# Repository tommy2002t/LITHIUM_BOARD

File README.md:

# LITHIUM_BOARD
# LITHIUM_BOARD

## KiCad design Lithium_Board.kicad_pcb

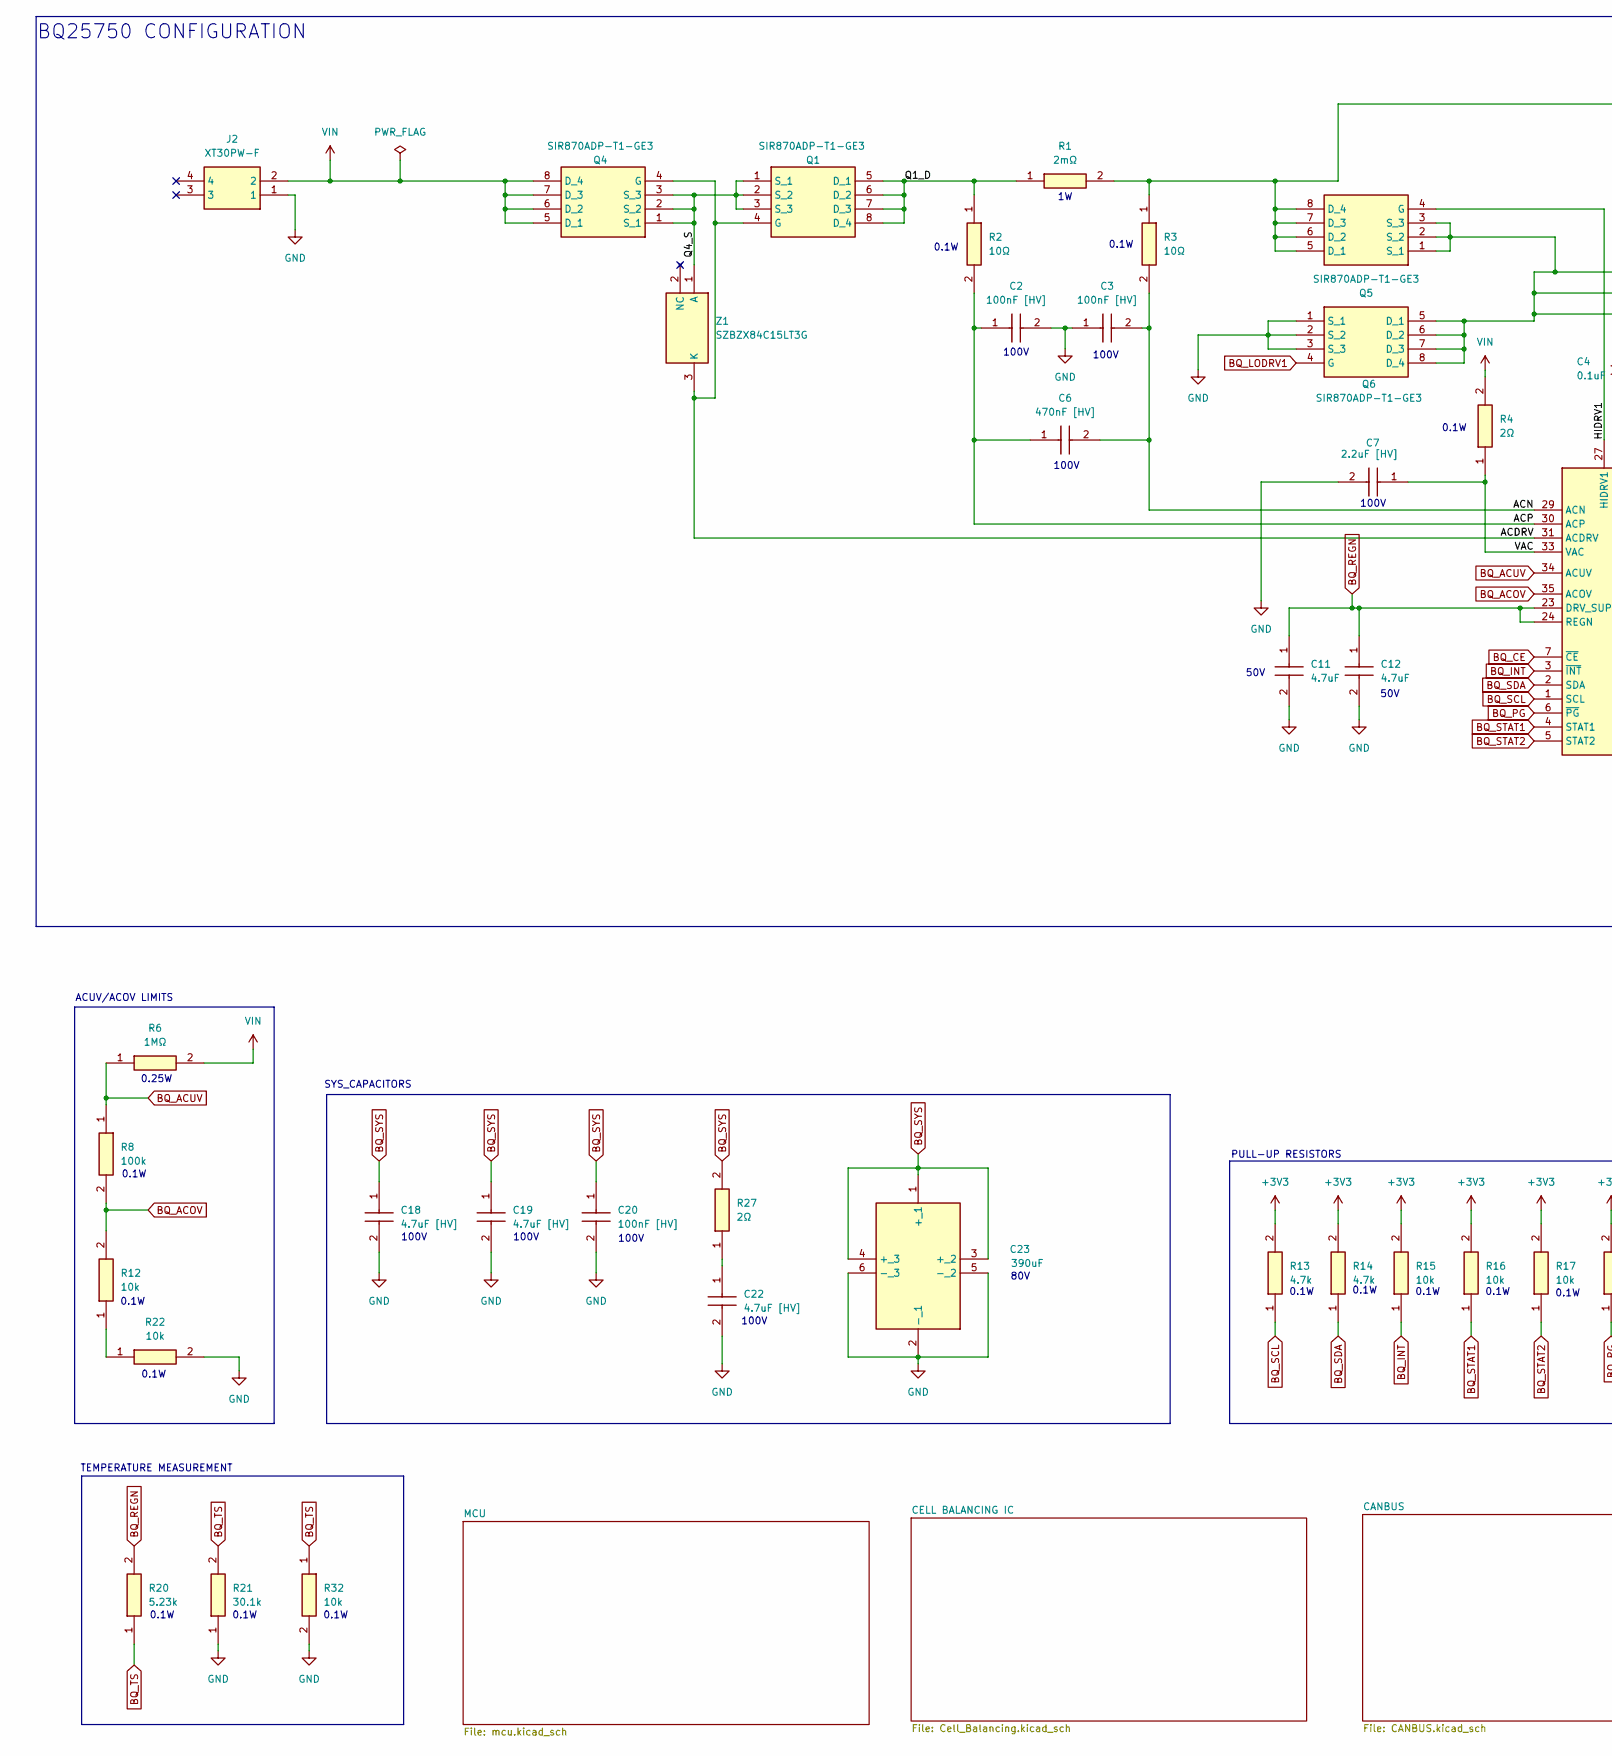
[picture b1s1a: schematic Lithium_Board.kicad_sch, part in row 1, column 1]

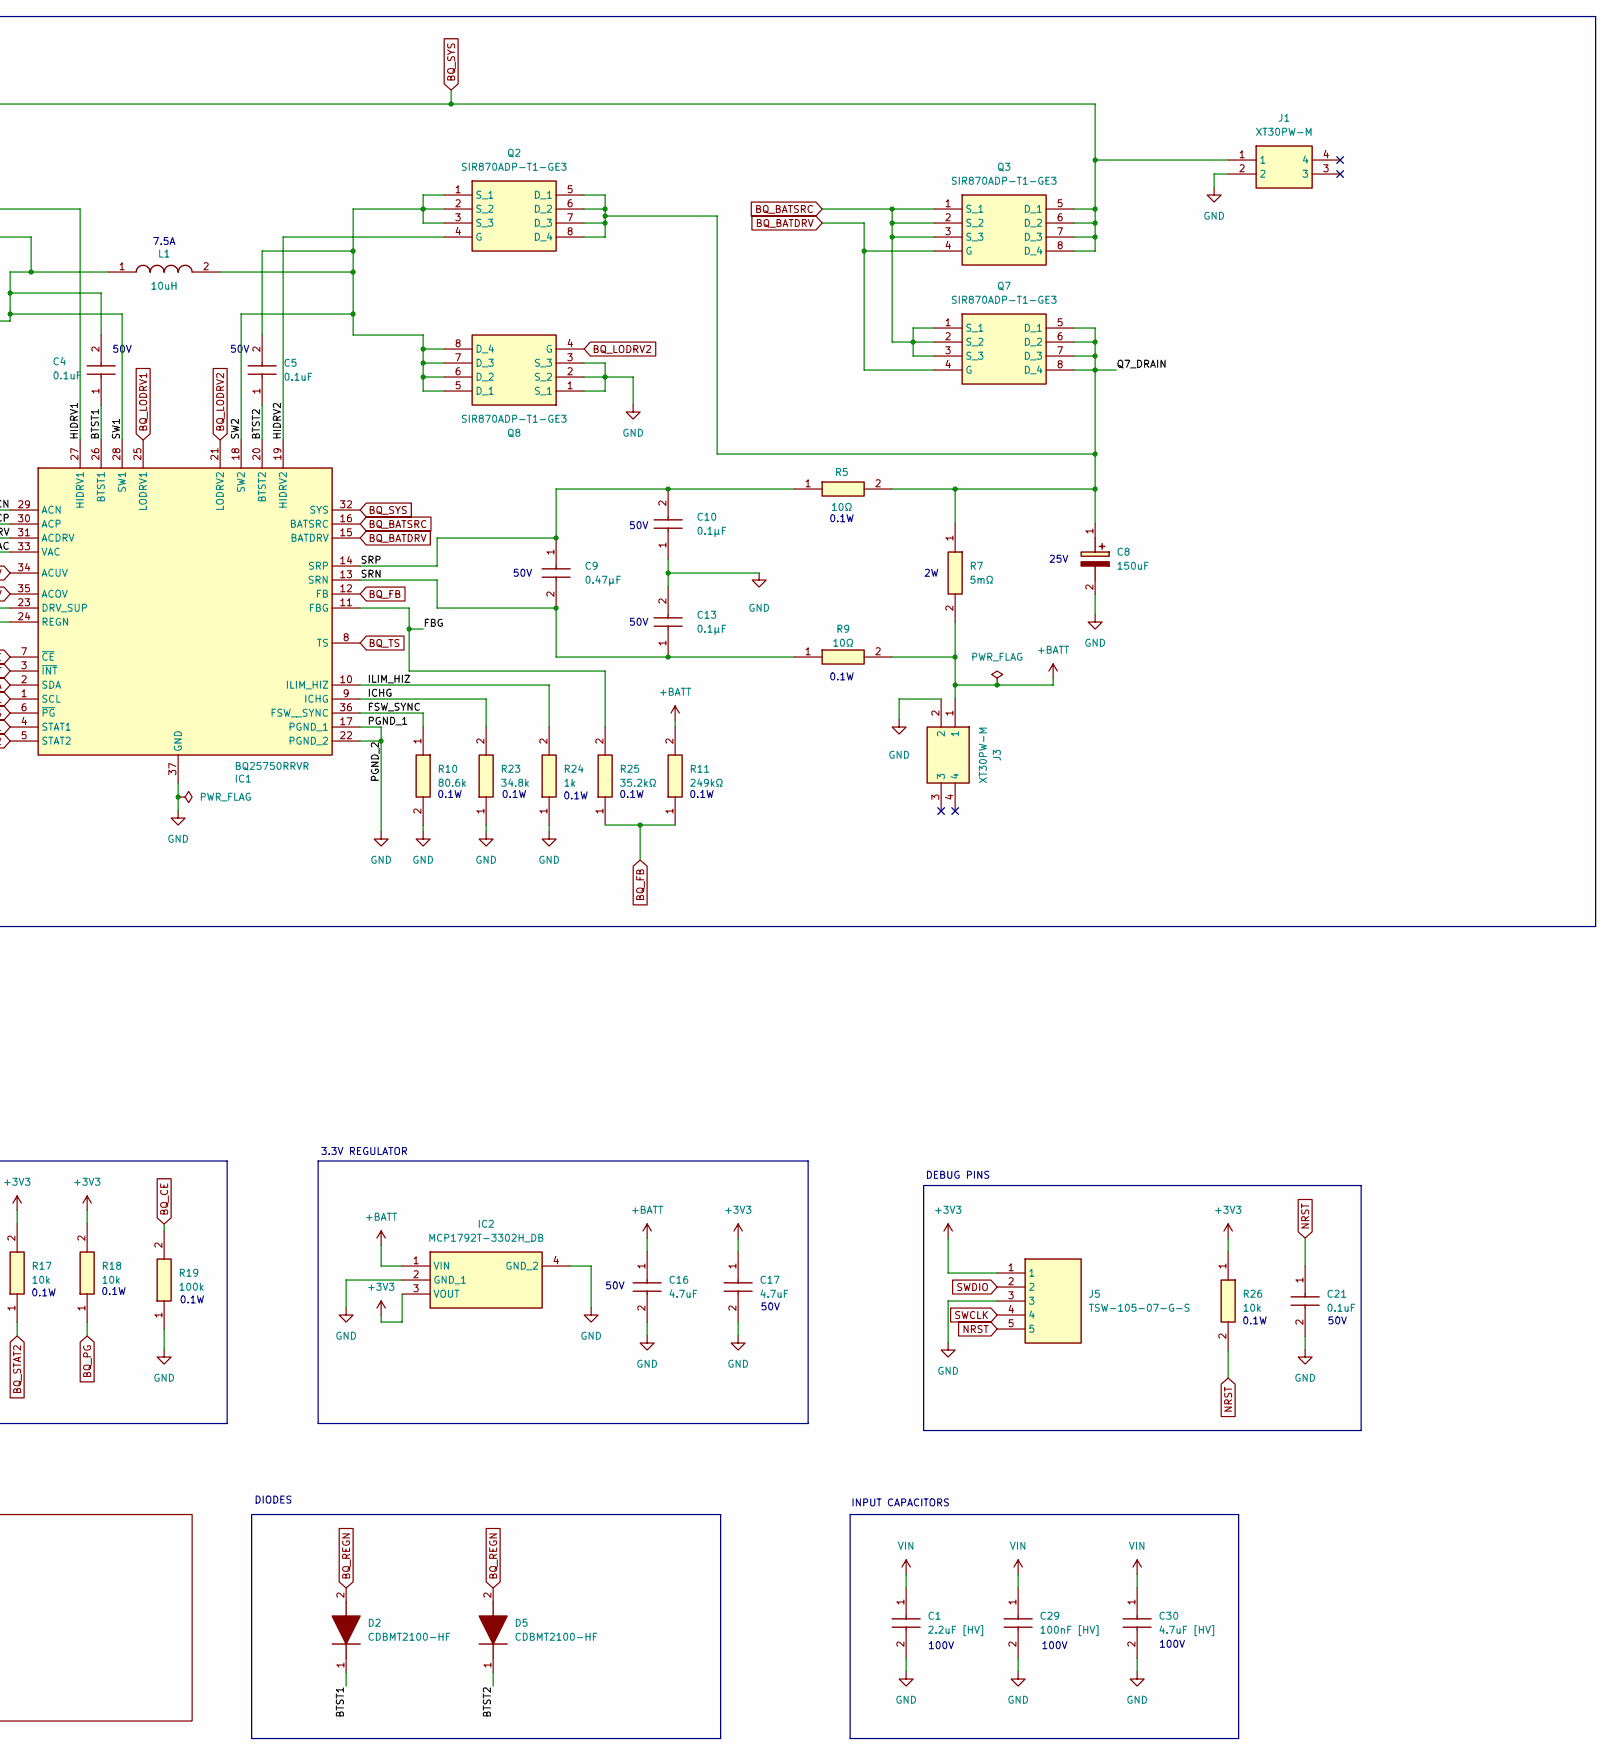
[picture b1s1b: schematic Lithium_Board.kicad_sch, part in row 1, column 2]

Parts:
C1, C7: 2.2uF [HV]; CAPC3216X180N; Mouser Part Number 187-CL31B225KCHSNNE
C2, C3, C20, C29: 100nF [HV]; CAPC1608X95N; Mouser Part Number 80-C0603C104K1RAUTO
C4, C5, C21: 0.1uF; CAPC1608X90N; Mouser Part Number 603-CC603KRX7R9BB104
C6: 470nF [HV]; CAPC3216X190N; Mouser Part Number 810-CGA5L2X7R2A474K
C8: 150uF; EEEHP1H4R7P; Manufacturer_Part_Number EEH-ZL1E151P
C9: 0.47μF; C0805; Mouser Part Number 80-C0805X474K5REAUTO
C10, C13: 0.1μF; CAPC1608X90N; Mouser Part Number 603-CC603KRX7R9BB104
C11, C12, C16, C17: 4.7uF; CAPC3225X280N; Mouser Part Number 963-UMJ325AB7475KMHP
C18, C19, C22, C30: 4.7uF [HV]; CAPC3225X94N; Mouser Part Number 581-KAM32LR72A475KU
C23: 390uF; EEEFK0J682AV; Mouser Part Number 667-EEE-TP1K391V
D2, D5: CDBMT2100-HF; SODFL3516X100N; Mouser Part Number 750-CDBMT2100-HF
IC1: BQ25750RRVR; QFN50P500X600X100-37N-D; Mouser Part Number 595-BQ25750RRVR
IC2: MCP1792T-3302H_DB; SOT230P700X180-4N; Mouser Part Number 579-MCP1792T-3302HDB
J1, J3: XT30PW-M; XT30PWM; Manufacturer_Part_Number XT30PW-M
J2: XT30PW-F; XT30PWF; Manufacturer_Part_Number XT30PW-F
J5: TSW-105-07-G-S; TSW-105-XX-YY-S; Mouser Part Number 200-TSW10507GS
L1: 10uH; INDPM110100X400N; Mouser Part Number 652-SRP1038A-100M
Q1, Q2, Q3, Q4, Q5, Q6, Q7, Q8: SIR870ADP-T1-GE3; POWERPAK-SO-8; Mouser Part Number 78-SIR870ADP-T1-GE3
R1: 2mΩ; RESC3216X59N; Mouser Part Number 755-PMR18EZPFV2L00
R2, R3, R5, R9: 10Ω; RESC1608X55N; Mouser Part Number 603-RC0603FR-0710RL
R4, R27: 2Ω; RESC1608X55N; Mouser Part Number 603-RC0603FR-072RL
R6: 1MΩ; RESC3116X65N; Mouser Part Number 603-VT1206BRD071ML
R7: 5mΩ; RESC6432X67N; Mouser Part Number 755-PMR100HZPFU5L00
R8, R19: 100k; RESC1608X55N; Mouser Part Number 603-RC0603FR-07100KL
R10: 80.6k; RESC1608X55N; Mouser Part Number 603-RC0603FR-0780K6L
R11: 249kΩ; RESC1608X55N; Mouser Part Number 603-RT0603BRD07249KL
R12, R15, R16, R17, R18, R22, R26, R32: 10k; RESC1608X55N; Mouser Part Number 603-RC0603FR-0710KL
R13, R14: 4.7k; RESC1608X55N; Mouser Part Number 603-RC0603FR-074K7L
R20: 5.23k; RESC1608X55N; Mouser Part Number 603-RC0603FR-075K23L
R21: 30.1k; RESC1608X55N; Mouser Part Number 603-RC0603FR-0730K1L
R23: 34.8k; RESC1608X55N; Mouser Part Number 603-RC0603FR-0734K8L
R24: 1k; RESC1608X55N; Mouser Part Number 603-RC0603FR-071KL
R25: 35.2kΩ; RESC1608X55N; Manufacturer_Part_Number RT0603BRD0735K2L
Z1: SZBZX84C15LT3G; SOT96P237X111-3N; Mouser Part Number 863-SZBZX84C15LT3G

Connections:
+3V3: C17.1, IC2.3 (VOUT), J5.1, R13.2, R14.2, R15.2, R16.2, R17.2, R18.2, R26.1; also elsewhere on the board
+BATT: C16.1, IC2.1 (VIN), J3.1, R7.2, R9.2, R11.2
/ACDRV: IC1.31 (ACDRV), Q1.4 (G), Q4.4 (G), Z1.3 (K)
/ACN: C3.2, C6.2, IC1.29 (ACN), R3.2
/ACP: C2.1, C6.1, IC1.30 (ACP), R2.2
/BTST1: C4.1, D2.1 (K), IC1.26 (BTST1)
/BTST2: C5.1, D5.1 (K), IC1.20 (BTST2)
/FBG: IC1.11 (FBG), R25.2
/FSW_SYNC: IC1.36 (FSW__SYNC), R10.1
/HIDRV1: IC1.27 (HIDRV1), Q5.4 (G)
/HIDRV2: IC1.19 (HIDRV2), Q2.4 (G)
/ICHG: IC1.9 (ICHG), R23.2
/ILIM_HIZ: IC1.10 (ILIM_HIZ), R24.2
/Q1_D: Q1.5 (D_1), Q1.6 (D_2), Q1.7 (D_3), Q1.8 (D_4), R1.1, R2.1
/Q4_S: Q1.1 (S_1), Q1.2 (S_2), Q1.3 (S_3), Q4.1 (S_1), Q4.2 (S_2), Q4.3 (S_3), Z1.1 (A)
/Q7_DRAIN: C8.1 (+), Q2.5 (D_1), Q2.6 (D_2), Q2.7 (D_3), Q2.8 (D_4), Q7.5 (D_1), Q7.6 (D_2), Q7.7 (D_3), Q7.8 (D_4), R5.2, R7.1
/SRN: C9.2, C13.1, IC1.13 (SRN), R9.1
/SRP: C9.1, C10.2, IC1.14 (SRP), R5.1
/SW1: C4.2, IC1.28 (SW1), L1.1, Q5.1 (S_1), Q5.2 (S_2), Q5.3 (S_3), Q6.5 (D_1), Q6.6 (D_2), Q6.7 (D_3), Q6.8 (D_4)
/SW2: C5.2, IC1.18 (SW2), L1.2, Q2.1 (S_1), Q2.2 (S_2), Q2.3 (S_3), Q8.5 (D_1), Q8.6 (D_2), Q8.7 (D_3), Q8.8 (D_4)
/VAC: C7.1, IC1.33 (VAC), R4.1
BQ_ACOV: IC1.35 (ACOV), R8.2, R12.2
BQ_ACUV: IC1.34 (ACUV), R6.1, R8.1
BQ_BATDRV: IC1.15 (BATDRV), Q3.4 (G), Q7.4 (G)
BQ_BATSRC: IC1.16 (BATSRC), Q3.1 (S_1), Q3.2 (S_2), Q3.3 (S_3), Q7.1 (S_1), Q7.2 (S_2), Q7.3 (S_3)
BQ_CE: IC1.7 (~CE), R19.2; also elsewhere on the board
BQ_FB: IC1.12 (FB), R11.1, R25.1
BQ_INT: IC1.3 (~INT), R15.1; also elsewhere on the board
BQ_LODRV1: IC1.25 (LODRV1), Q6.4 (G)
BQ_LODRV2: IC1.21 (LODRV2), Q8.4 (G)
BQ_PG: IC1.6 (~PG), R18.1; also elsewhere on the board
BQ_REGN: C11.1, C12.1, D2.2 (A), D5.2 (A), IC1.23 (DRV_SUP), IC1.24 (REGN), R20.2
BQ_SCL: IC1.1 (SCL), R13.1; also elsewhere on the board
BQ_SDA: IC1.2 (SDA), R14.1; also elsewhere on the board
BQ_STAT1: IC1.4 (STAT1), R16.1; also elsewhere on the board
BQ_STAT2: IC1.5 (STAT2), R17.1; also elsewhere on the board
BQ_SYS: C18.1, C19.1, C20.1, C23.1 (+_1), C23.3 (+_2), C23.4 (+_3), IC1.32 (SYS), J1.1, Q3.5 (D_1), Q3.6 (D_2), Q3.7 (D_3), Q3.8 (D_4), Q5.5 (D_1), Q5.6 (D_2), Q5.7 (D_3), Q5.8 (D_4), R1.2, R3.1, R27.2
BQ_TS: IC1.8 (TS), R20.1, R21.2, R32.1; also elsewhere on the board
GND: C1.2, C2.2, C3.1, C7.2, C8.2 (-), C10.1, C11.2, C12.2, C13.2, C16.2, C17.2, C18.2, C19.2, C20.2, C21.2, C22.2, C23.2 (-_1), C23.5 (-_2), C23.6 (-_3), C29.2, C30.2, IC1.17 (PGND_1), IC1.22 (PGND_2), IC1.37 (GND), IC2.2 (GND_1), IC2.4 (GND_2), J1.2, J2.1, J3.2, J5.3, Q6.1 (S_1), Q6.2 (S_2), Q6.3 (S_3), Q8.1 (S_1), Q8.2 (S_2), Q8.3 (S_3), R10.2, R19.1, R21.1, R22.2, R23.1, R24.1, R32.2; also elsewhere on the board
NRST: C21.1, J5.5, R26.2; also elsewhere on the board
unnamed: C22.1, R27.1
unnamed: R12.1, R22.1
SWCLK: J5.4; also elsewhere on the board
SWDIO: J5.2; also elsewhere on the board
VIN: C1.1, C29.1, C30.1, J2.2, Q4.5 (D_1), Q4.6 (D_2), Q4.7 (D_3), Q4.8 (D_4), R4.2, R6.2

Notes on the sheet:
0.1W
TEMPERATURE MEASUREMENT
50V
ACUV/ACOV LIMITS
INPUT CAPACITORS
100V
PULL-UP RESISTORS
DEBUG PINS
7.5A
3.3V REGULATOR
DIODES
25V
80V
SYS_CAPACITORS
0.25W
BQ25750 CONFIGURATION

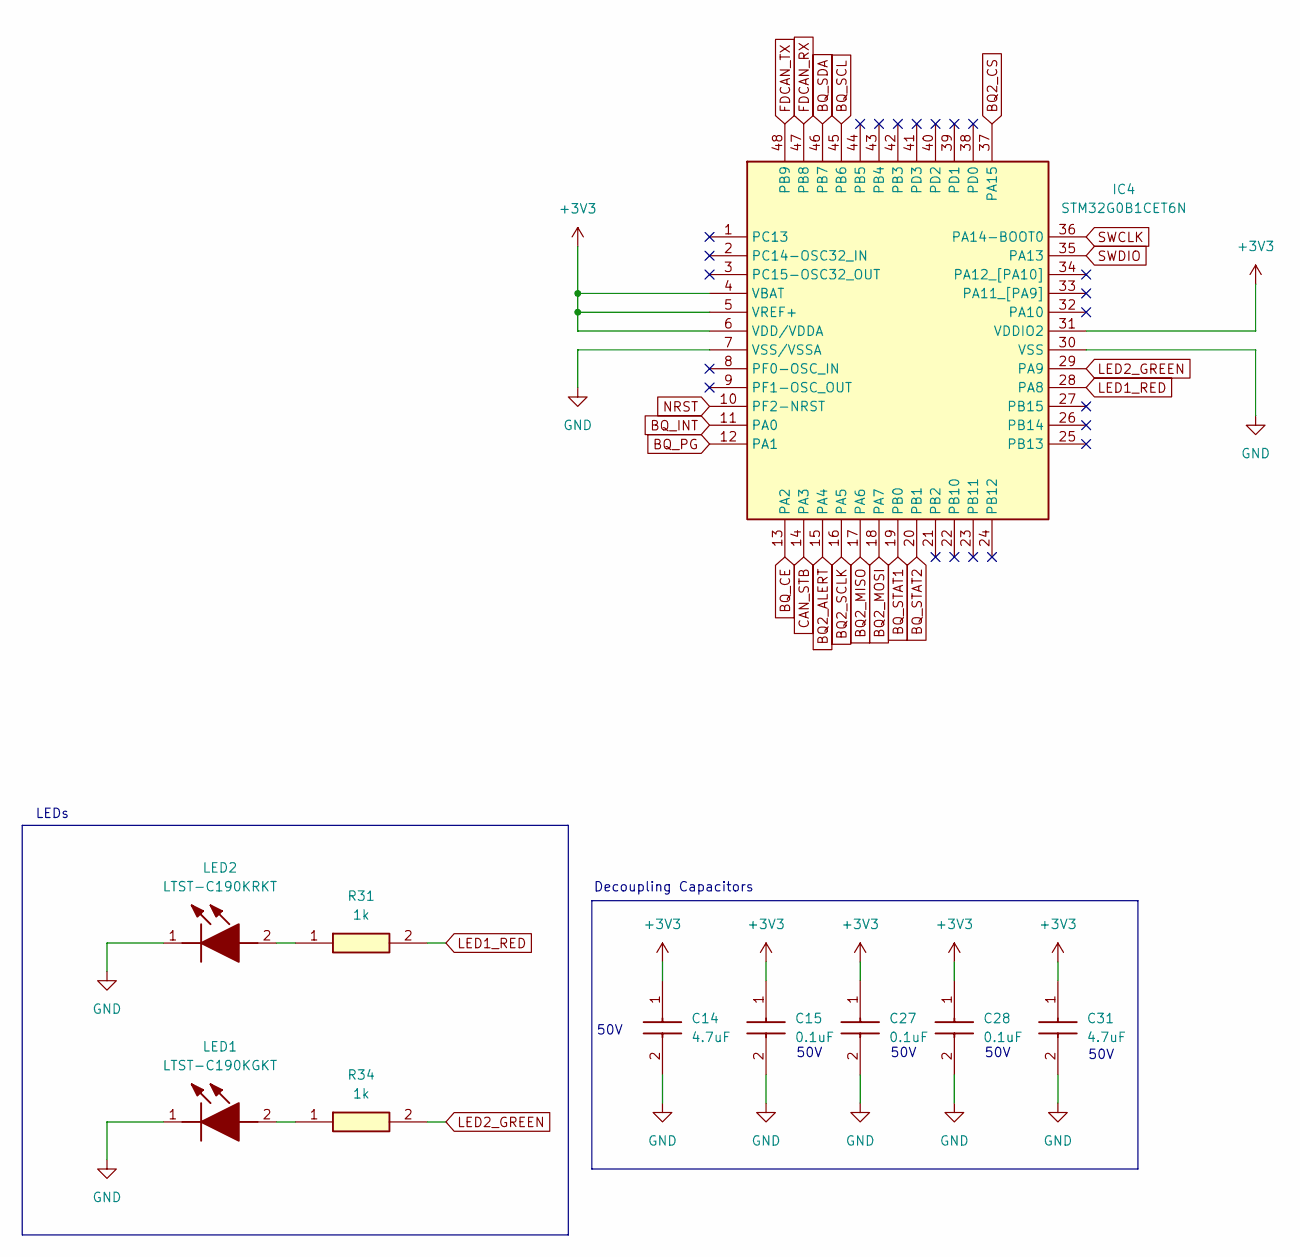
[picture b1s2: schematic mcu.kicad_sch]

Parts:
C14, C31: 4.7uF; CAPC3225X280N; Mouser Part Number 963-UMJ325AB7475KMHP
C15, C27, C28: 0.1uF; CAPC1608X90N; Mouser Part Number 603-CC603KRX7R9BB104
IC4: STM32G0B1CET6N; QFP50P900X900X160-48N; Mouser Part Number 511-STM32G0B1CET6N
LED1: LTST-C190KGKT; LEDC1608X80N; Mouser Part Number 859-LTST-C190KGKT
LED2: LTST-C190KRKT; LEDC1608X80N; Mouser Part Number 859-LTST-C190KRKT
R31, R34: 1k; RESC1608X55N; Mouser Part Number 603-RC0603FR-071KL

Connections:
+3V3: C14.1, C15.1, C27.1, C28.1, C31.1, IC4.4 (VBAT), IC4.5 (VREF+), IC4.6 (VDD/VDDA), IC4.31 (VDDIO2); also elsewhere on the board
BQ2_ALERT: IC4.15 (PA4); also elsewhere on the board
BQ2_CS: IC4.37 (PA15); also elsewhere on the board
BQ2_MISO: IC4.17 (PA6); also elsewhere on the board
BQ2_MOSI: IC4.18 (PA7); also elsewhere on the board
BQ2_SCLK: IC4.16 (PA5); also elsewhere on the board
BQ_CE: IC4.13 (PA2); also elsewhere on the board
BQ_INT: IC4.11 (PA0); also elsewhere on the board
BQ_PG: IC4.12 (PA1); also elsewhere on the board
BQ_SCL: IC4.45 (PB6); also elsewhere on the board
BQ_SDA: IC4.46 (PB7); also elsewhere on the board
BQ_STAT1: IC4.19 (PB0); also elsewhere on the board
BQ_STAT2: IC4.20 (PB1); also elsewhere on the board
CAN_STB: IC4.14 (PA3); also elsewhere on the board
FDCAN_RX: IC4.47 (PB8); also elsewhere on the board
FDCAN_TX: IC4.48 (PB9); also elsewhere on the board
GND: C14.2, C15.2, C27.2, C28.2, C31.2, IC4.7 (VSS/VSSA), IC4.30 (VSS), LED1.1 (K), LED2.1 (K); also elsewhere on the board
LED1_RED: IC4.28 (PA8), R31.2
LED2_GREEN: IC4.29 (PA9), R34.2
NRST: IC4.10 (PF2-NRST); also elsewhere on the board
unnamed: LED1.2 (A), R34.1
unnamed: LED2.2 (A), R31.1
SWCLK: IC4.36 (PA14-BOOT0); also elsewhere on the board
SWDIO: IC4.35 (PA13); also elsewhere on the board

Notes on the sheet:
Decoupling Capacitors
50V
LEDs

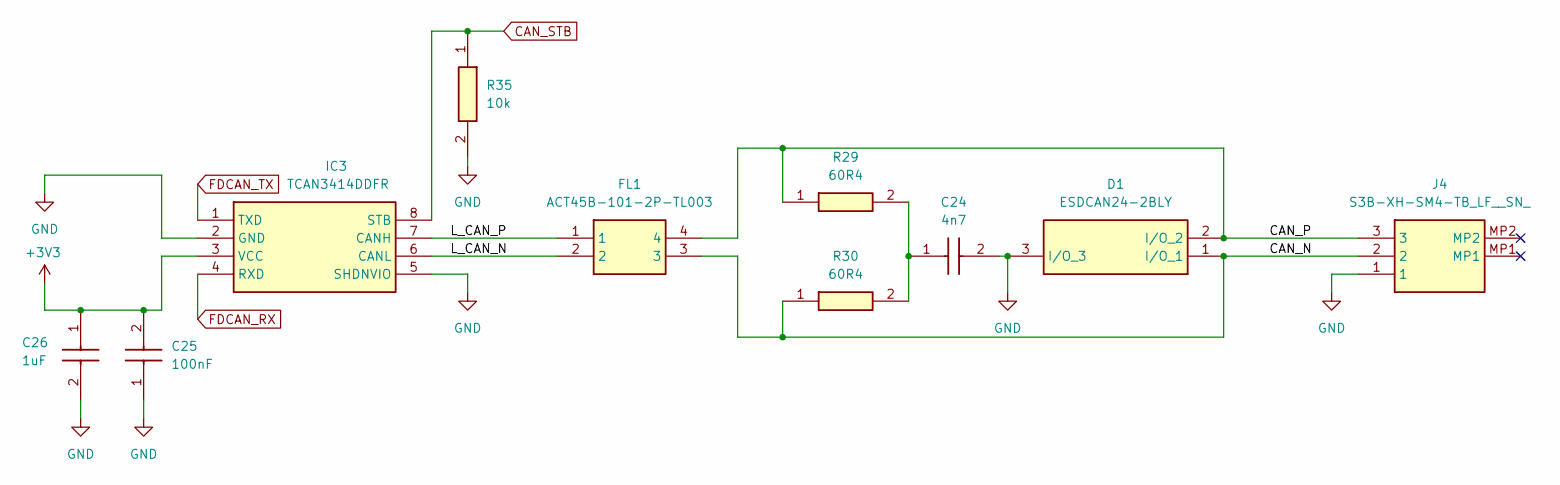
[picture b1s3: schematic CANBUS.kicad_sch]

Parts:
C24: 4n7; CAPC1608X90N; Mouser Part Number 81-GRM188R72A472KA1D
C25: 100nF; GRM15x; Mouser Part Number 81-GRM155R71H104KE4J
C26: 1uF; CAPC2012X145N; Mouser Part Number 810-C2012X7R1H105K
D1: ESDCAN24-2BLY; SOT95P255X125-3N; Mouser Part Number 511-ESDCAN24-2BLY
FL1: ACT45B-101-2P-TL003; ACT45B1012PTL003; Mouser Part Number 810-ACT45B1012PTL003
IC3: TCAN3414DDFR; INA190A2NDDFREP; Mouser Part Number 595-TCAN3414DDFR
J4: S3B-XH-SM4-TB_LF__SN_; S3BXHSM4TBLFSN; Mouser Part Number N/A
R29, R30: 60R4; ERJ2RKD1004X; Mouser Part Number 667-ERJ-2RKF60R4X
R35: 10k; RESC1608X55N; Mouser Part Number 603-RC0603FR-0710KL

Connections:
+3V3: C25.2, C26.1, IC3.3 (VCC); also elsewhere on the board
/CANBUS/CAN_N: D1.1 (I/O), FL1.3, J4.2, R30.1
/CANBUS/CAN_P: D1.2 (I/O), FL1.4, J4.3, R29.1
/CANBUS/L_CAN_N: FL1.2, IC3.6 (CANL)
/CANBUS/L_CAN_P: FL1.1, IC3.7 (CANH)
CAN_STB: IC3.8 (STB), R35.1; also elsewhere on the board
FDCAN_RX: IC3.4 (RXD); also elsewhere on the board
FDCAN_TX: IC3.1 (TXD); also elsewhere on the board
GND: C24.2, C25.1, C26.2, D1.3 (I/O), IC3.2 (GND), IC3.5 (SHDNVIO), J4.1, R35.2; also elsewhere on the board
unnamed: C24.1, R29.2, R30.2

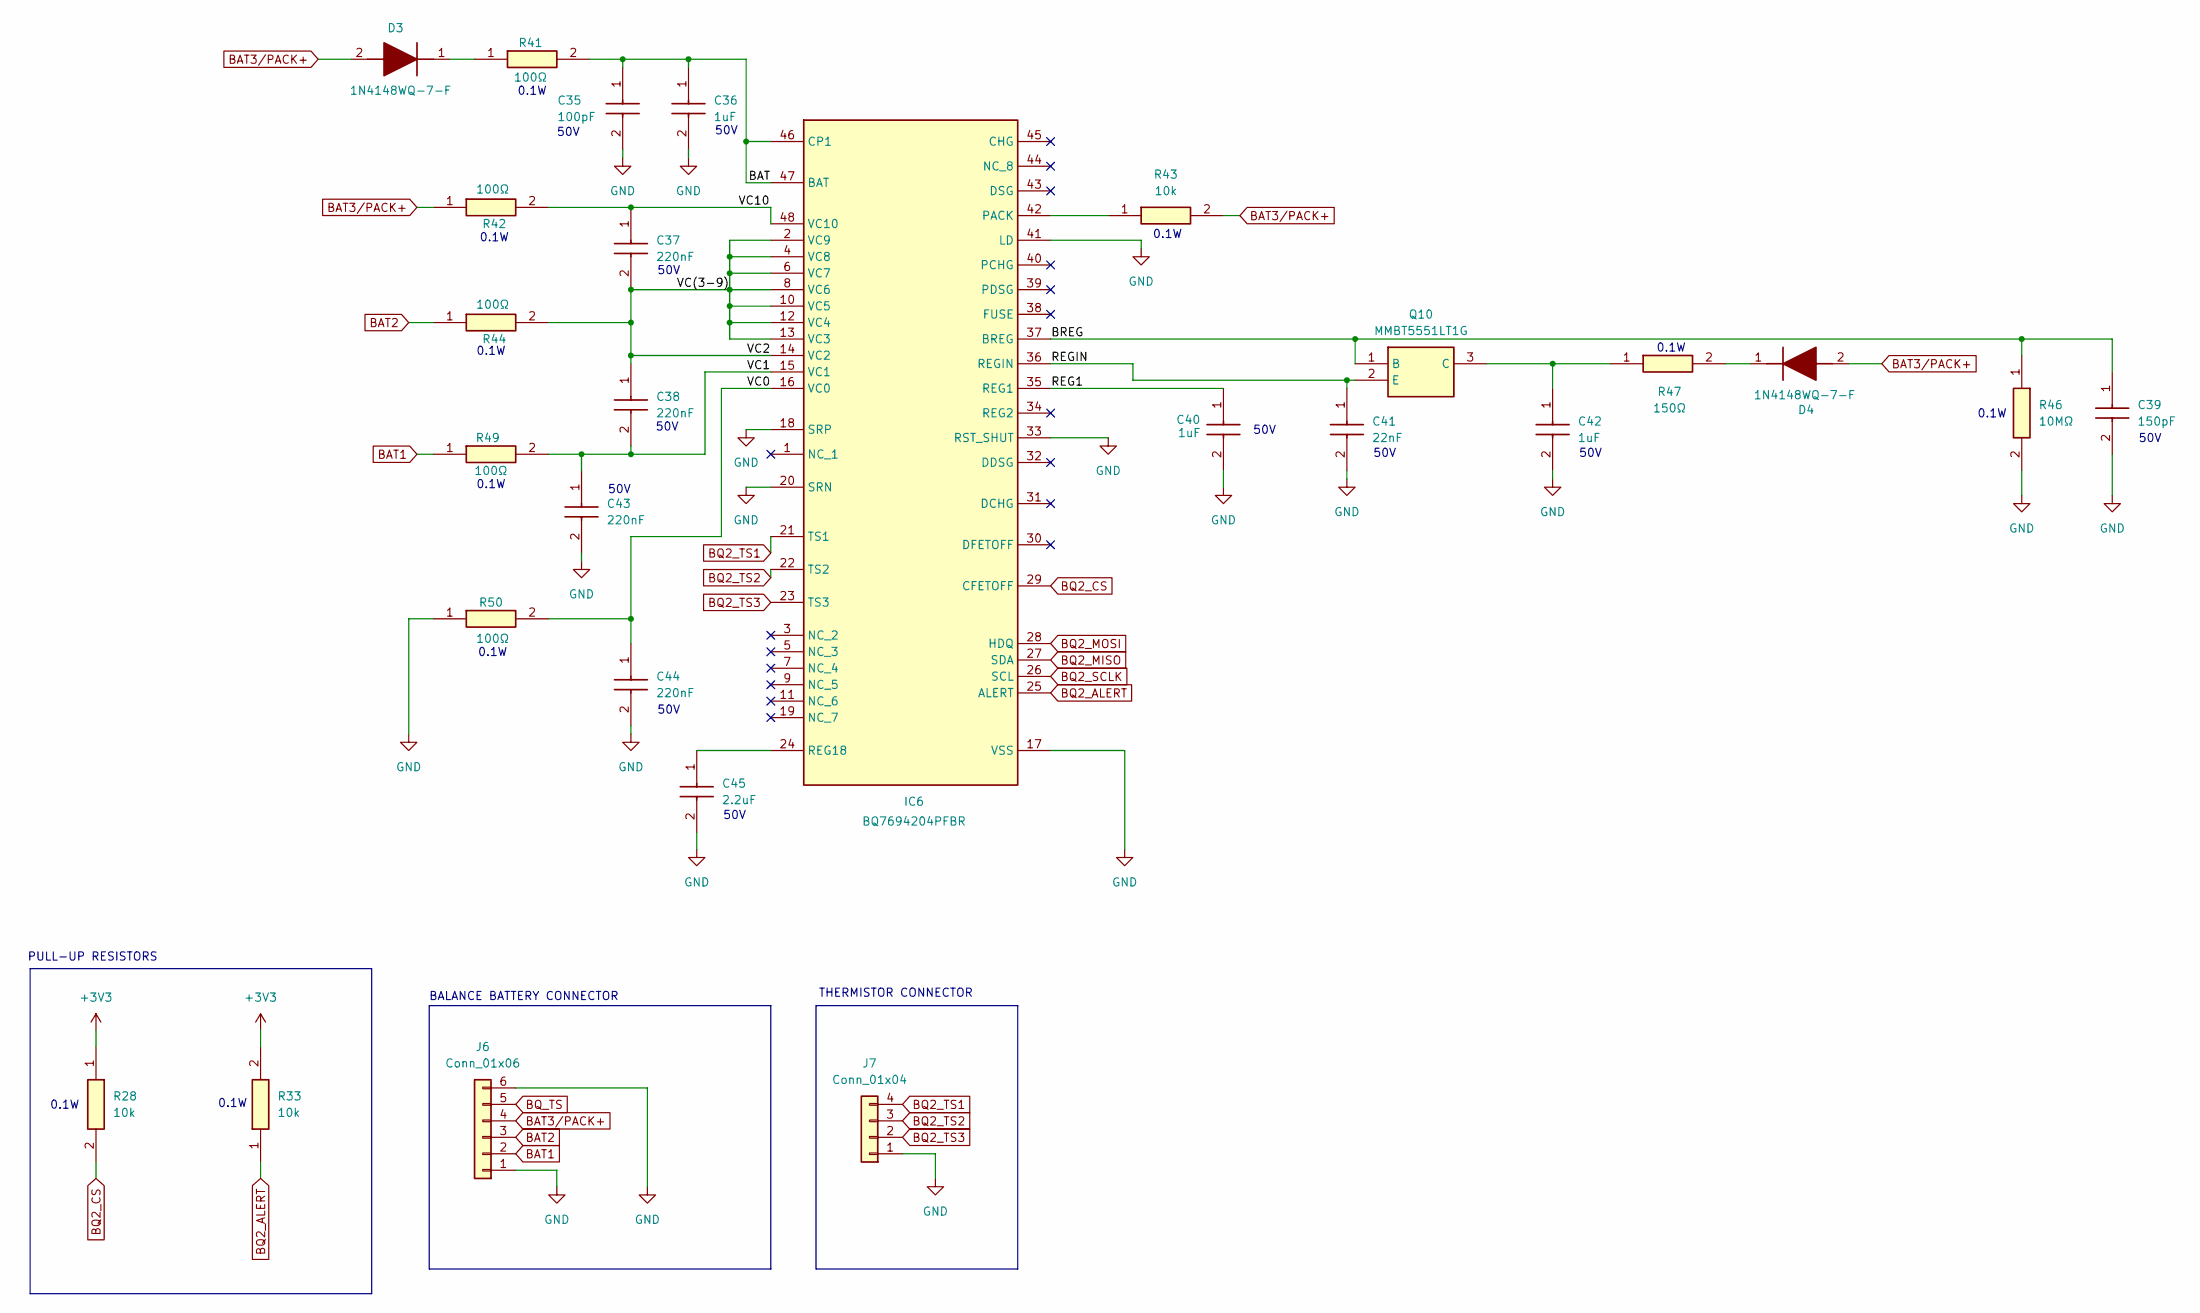
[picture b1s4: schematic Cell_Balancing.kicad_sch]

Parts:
C35: 100pF; CAPC1608X87N; Mouser Part Number 80-C0603C101J5G
C36, C40, C42: 1uF; CAPC2012X145N; Mouser Part Number 810-C2012X7R1H105K
C37, C38, C43, C44: 220nF; C0805; Mouser Part Number 80-C0805C224K5R
C39: 150pF; CAPC1608X87N; Mouser Part Number 80-C0603C151J5G
C41: 22nF; C0603; Mouser Part Number 80-C0603C223K5R
C45: 2.2uF; C1206; Mouser Part Number 80-C1206C225K5R
D3, D4: 1N4148WQ-7-F; SOD3716X145N; Mouser Part Number 621-1N4148WQ-7-F
IC6: BQ7694204PFBR; QFP50P900X900X120-48N; Mouser Part Number 595-BQ7694204PFBR
J6: Conn_01x06; JST_XH_B6B-XH-A_1x06_P2.50mm_Vertical
J7: Conn_01x04; JST_XH_B4B-XH-A_1x04_P2.50mm_Vertical
Q10: MMBT5551LT1G; SOT96P237X111-3N; Mouser Part Number 863-MMBT5551LT1G
R28, R33, R43: 10k; RESC1608X55N; Mouser Part Number 603-RC0603FR-0710KL
R41, R42, R44, R49, R50: 100Ω; RESC1608X55N; Mouser Part Number 603-RC0603FR-07100RL
R46: 10MΩ; RESC1608X55N; Mouser Part Number 603-RC0603FR-0710ML
R47: 150Ω; RESC1608X55N; Mouser Part Number 603-RC0603FR-07150RL

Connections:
+3V3: R28.1, R33.2; also elsewhere on the board
/CELL BALANCING IC/BAT: C35.1, C36.1, IC6.46 (CP1), IC6.47 (BAT), R41.2
/CELL BALANCING IC/BREG: C39.1, IC6.37 (BREG), Q10.1 (B), R46.1
/CELL BALANCING IC/REG1: C40.1, IC6.35 (REG1)
/CELL BALANCING IC/REGIN: C41.1, IC6.36 (REGIN), Q10.2 (E)
/CELL BALANCING IC/VC0: C44.1, IC6.16 (VC0), R50.2
/CELL BALANCING IC/VC1: C38.2, C43.1, IC6.15 (VC1), R49.2
/CELL BALANCING IC/VC10: C37.1, IC6.48 (VC10), R42.2
/CELL BALANCING IC/VC(3-9): C37.2, C38.1, IC6.2 (VC9), IC6.4 (VC8), IC6.6 (VC7), IC6.8 (VC6), IC6.10 (VC5), IC6.12 (VC4), IC6.13 (VC3), IC6.14 (VC2), R44.2
BAT1: J6.2, R49.1
BAT2: J6.3, R44.1
BAT3/PACK+: D3.2 (A), D4.2 (A), J6.4, R42.1, R43.2
BQ2_ALERT: IC6.25 (ALERT), R33.1; also elsewhere on the board
BQ2_CS: IC6.29 (CFETOFF), R28.2; also elsewhere on the board
BQ2_MISO: IC6.27 (SDA); also elsewhere on the board
BQ2_MOSI: IC6.28 (HDQ); also elsewhere on the board
BQ2_SCLK: IC6.26 (SCL); also elsewhere on the board
BQ2_TS1: IC6.21 (TS1), J7.4
BQ2_TS2: IC6.22 (TS2), J7.3
BQ2_TS3: IC6.23 (TS3), J7.2
BQ_TS: J6.5; also elsewhere on the board
GND: C35.2, C36.2, C39.2, C40.2, C41.2, C42.2, C43.2, C44.2, C45.2, IC6.17 (VSS), IC6.18 (SRP), IC6.20 (SRN), IC6.33 (RST_SHUT), IC6.41 (LD), J6.1, J6.6, J7.1, R46.2, R50.1; also elsewhere on the board
unnamed: D3.1 (K), R41.1
unnamed: D4.1 (K), R47.2
unnamed: IC6.42 (PACK), R43.1
unnamed: C45.1, IC6.24 (REG18)
unnamed: C42.1, Q10.3 (C), R47.1

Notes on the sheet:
50V
0.1W
PULL-UP RESISTORS
BALANCE BATTERY CONNECTOR
THERMISTOR CONNECTOR

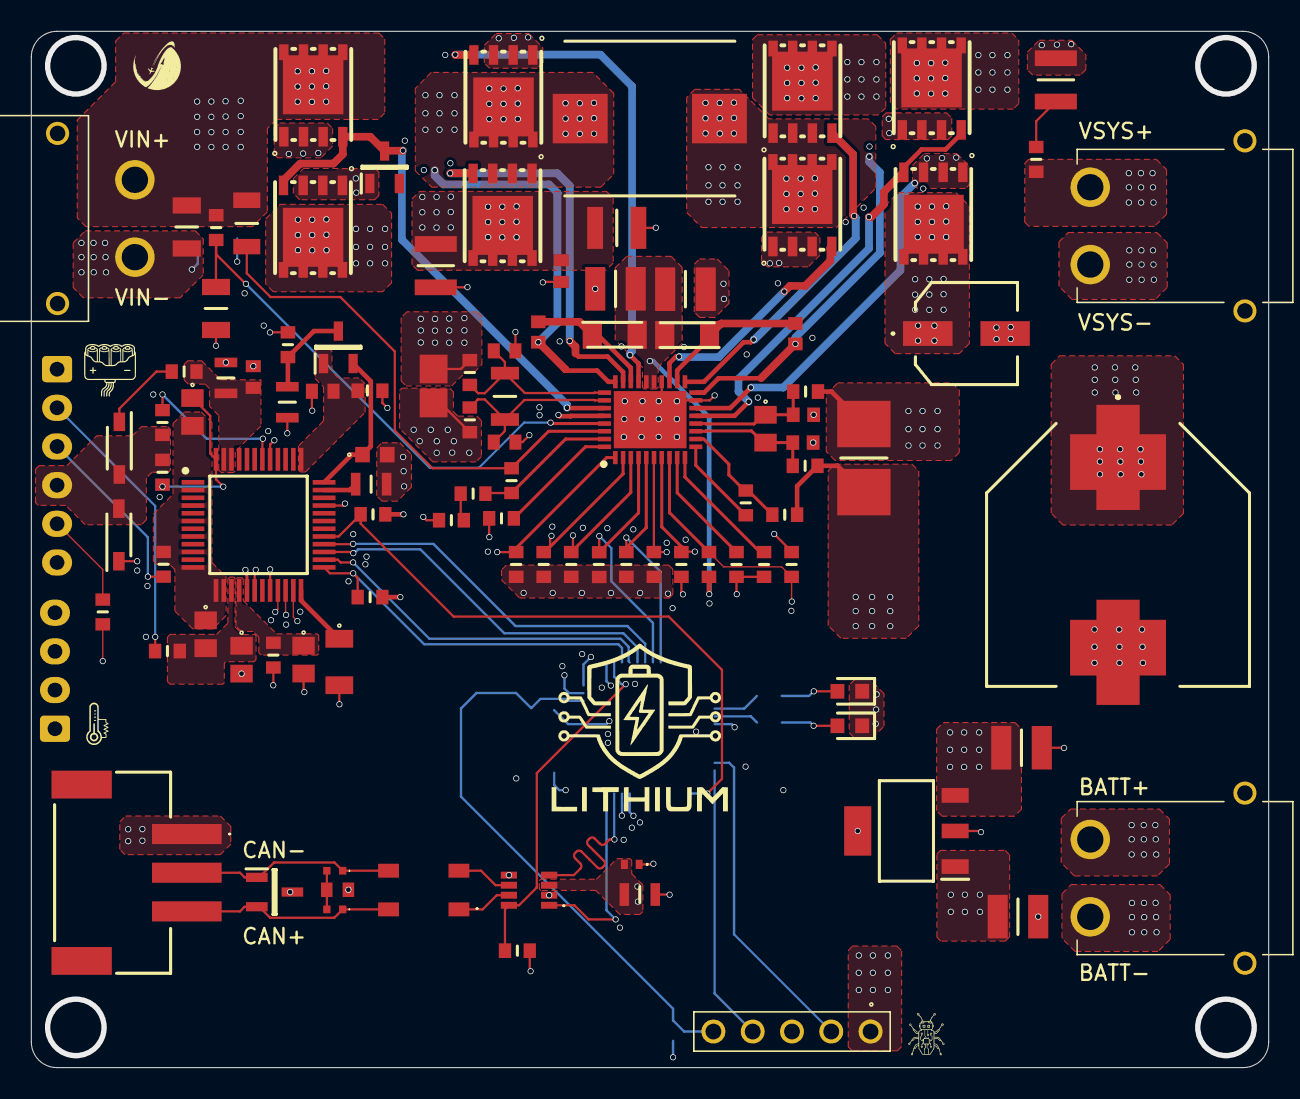
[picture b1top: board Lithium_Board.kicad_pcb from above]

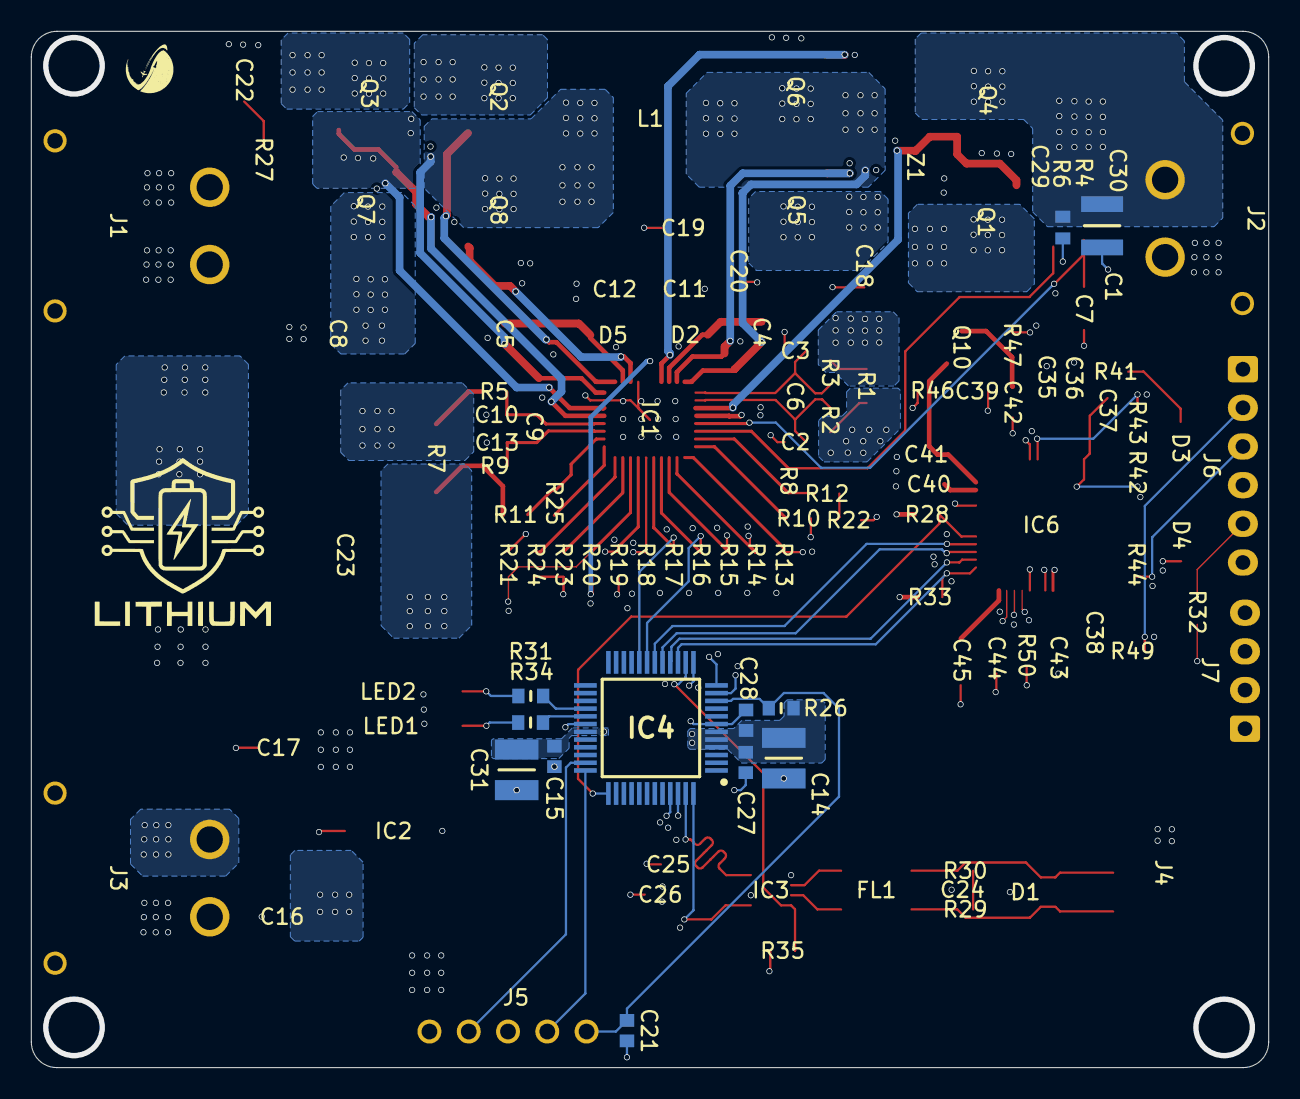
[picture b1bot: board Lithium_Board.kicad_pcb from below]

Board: 6 copper layers, 80.0 x 67.0 mm, 116 parts (12 on the bottom side), 81 nets.

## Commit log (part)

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2026-05-30 LITHIUM_Schematic_1.0
2026-05-30 First_Update
2026-05-31 Added CELL BALANCING IC
2026-05-31 Added Hierarchical Sheets
2026-05-31 Got rid of zip
2026-05-31 First Layout Try
2026-06-01 Added Ratings+Net Labels+First Layout Try+Calculations Excel
2026-06-03 New Cleaner Layout + Cell Balancing Connector
2026-06-06 Added Canbus+LEDs+New STM32
2026-06-06 Added Single-Cell Thermistor Pins
2026-06-07 Added New Potential Layout
2026-06-09 Wrong Side Longer Layout
2026-06-09 First Actual Design (No Return Vias, no Logo)
2026-06-10 First Layout Completed
2026-06-14 First Changes
2026-06-20 3D MODELS ADDED
2026-06-20 NEW 3D MODELS
2026-06-20 Final PERFECT design before big changes
2026-06-22 New Placement and Polygons
2026-06-22 LITHIUM V2 Placement
2026-06-22 New Design Placement
2026-06-22 Final LITHIUM Design V2
2026-06-22 Added New Layout Polygons+Routing
2026-06-23 Differential Routing
2026-06-24 CANBUS FIXED
2026-06-24 Perfected Polygons
2026-06-25 Added Return Vias
2026-06-26 Small Changes
2026-06-28 TS fixed + Small Changes
2026-06-28 Fixed Step File
2026-06-30 Mini Review Changes
